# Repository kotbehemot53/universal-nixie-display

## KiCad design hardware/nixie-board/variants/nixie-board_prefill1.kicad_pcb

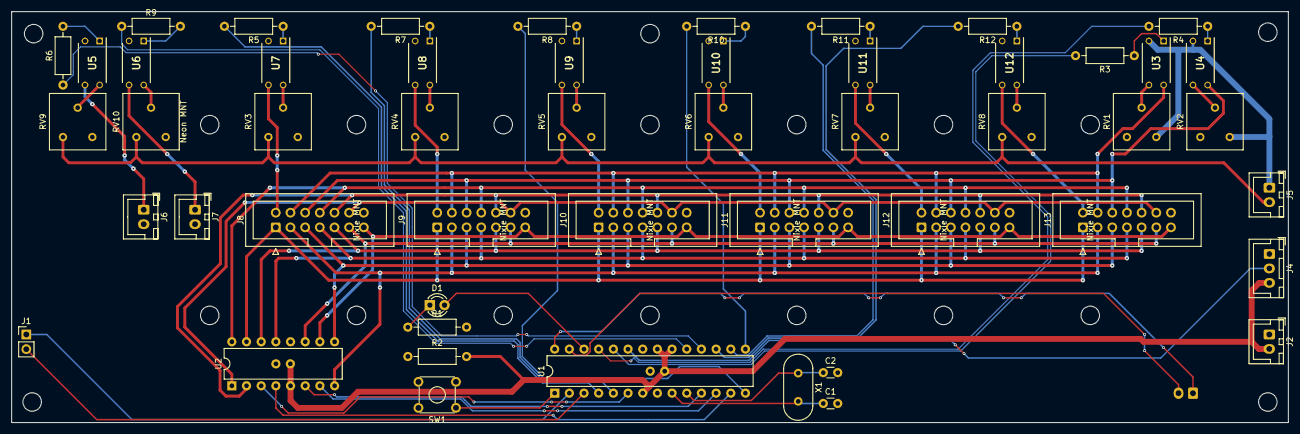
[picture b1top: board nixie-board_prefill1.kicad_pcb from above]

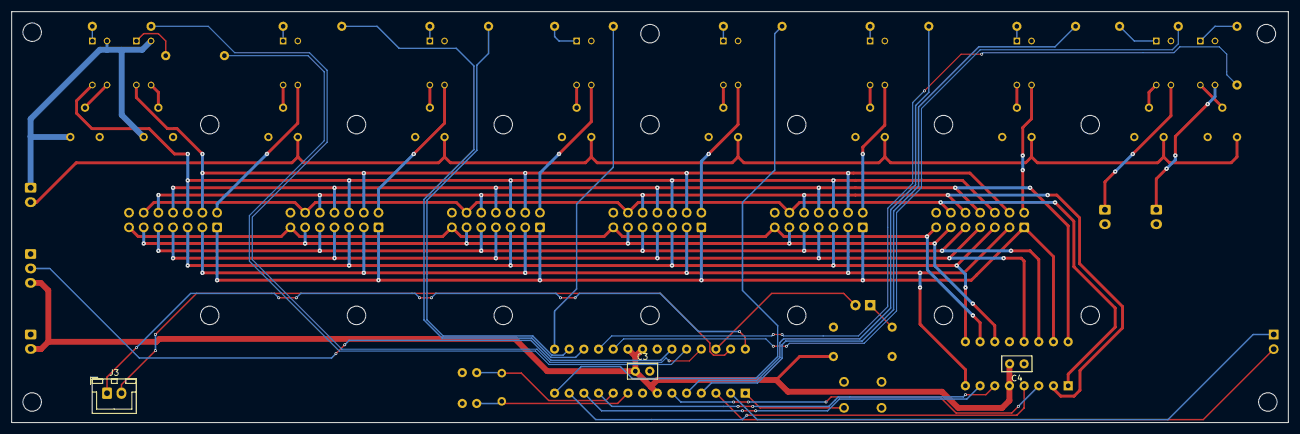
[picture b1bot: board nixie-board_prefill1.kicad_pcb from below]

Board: 2 copper layers, 221.0 x 71.1 mm, 54 parts (3 on the bottom side), 67 nets.

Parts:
C1, C2: 22pF; C_Disc_D3.0mm_W1.6mm_P2.50mm
C3, C4: 0.1uF; C_Disc_D5.0mm_W2.5mm_P2.50mm
D1: LED; LED_D3.0mm
J1: UART; PinHeader_1x02_P2.54mm_Vertical
J2: PWR; JST_XH_B2B-XH-A_1x02_P2.50mm_Vertical
J3: I2C DATA; JST_XH_B2B-XH-A_1x02_P2.50mm_Vertical
J4: BOOST C LV; JST_XH_B3B-XH-A_1x03_P2.50mm_Vertical
J5: BOOST C HV; JST_XH_B2B-XH-A_1x02_P2.50mm_Vertical
J6: NEON N0; JST_XH_B2B-XH-A_1x02_P2.50mm_Vertical
J7: NEON N1; JST_XH_B2B-XH-A_1x02_P2.50mm_Vertical
J8: L0; IDC-Header_2x07_P2.54mm_Vertical_alt_pins
J9: L1; IDC-Header_2x07_P2.54mm_Vertical_alt_pins
J10: L2; IDC-Header_2x07_P2.54mm_Vertical_alt_pins
J11: L3; IDC-Header_2x07_P2.54mm_Vertical_alt_pins
J12: L4; IDC-Header_2x07_P2.54mm_Vertical_alt_pins
J13: L5; IDC-Header_2x07_P2.54mm_Vertical_alt_pins
R1, R3, R4, R5, R6, R7, R8, R9, R10, R11, R12: 330; R_Axial_DIN0207_L6.3mm_D2.5mm_P10.16mm_Horizontal
R2: 10k; R_Axial_DIN0207_L6.3mm_D2.5mm_P10.16mm_Horizontal
RV1, RV2, RV9, RV10: 200k; Potentiometer_Bourns_3386F_Vertical
RV3, RV4, RV5, RV6, RV7, RV8: 10k; Potentiometer_Bourns_3386F_Vertical
SW1: RESET; SW_TH_Tactile_Omron_B3F-10xx
U1: ATmega328-P; DIP-28_W7.62mm
U2: K155NA1; DIP-16_W7.62mm
U3: L COMMA OPTCPLR; DIP762W56P254L469H470Q4N
U4: R COMMA OPTCPLR; DIP762W56P254L469H470Q4N
U5: N0 NEON SWITCH; DIP762W56P254L469H470Q4N
U6: N1 NEON SWITCH; DIP762W56P254L469H470Q4N
U7, U8, U9, U10, U11, U12: SFH619A; DIP762W56P254L469H470Q4N
X1: 16Mhz; Crystal_HC49-4H_Vertical

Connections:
+5V: C3.1, C4.2, J2.2, J4.3, R2.2, U1.7 (VCC), U1.20 (AVCC), U1.21 (AREF), U2.5 (VCC)
/0: J8.11 (0), J9.11 (0), J10.11 (0), J11.11 (0), J12.11 (0), J13.11 (0), U2.16 (0)
/1: J8.1, J9.1, J10.1, J11.1, J12.1, J13.1, U2.15 (1)
/2: J8.2, J9.2, J10.2, J11.2, J12.2, J13.2, U2.8 (2)
/3: J8.3, J9.3, J10.3, J11.3, J12.3, J13.3, U2.9 (3)
/4: J8.4, J9.4, J10.4, J11.4, J12.4, J13.4, U2.13 (4)
/5: J8.5, J9.5, J10.5, J11.5, J12.5, J13.5, U2.14 (5)
/6: J8.6, J9.6, J10.6, J11.6, J12.6, J13.6, U2.11 (6)
/7: J8.7, J9.7, J10.7, J11.7, J12.7, J13.7, U2.10 (7)
/8: J8.9 (8), J9.9 (8), J10.9 (8), J11.9 (8), J12.9 (8), J13.9 (8), U2.1 (8)
/9: J8.10 (9), J9.10 (9), J10.10 (9), J11.10 (9), J12.10 (9), J13.10 (9), U2.2 (9)
/A: U1.6 (PD4), U2.3 (A)
/B: U1.11 (PD5), U2.6 (B)
/C: U1.12 (PD6), U2.7 (C)
/CL: J8.13 (CL), J9.13 (CL), J10.13 (CL), J11.13 (CL), J12.13 (CL), J13.13 (CL), U3.4 (C_2)
/CR: J8.12 (CR), J9.12 (CR), J10.12 (CR), J11.12 (CR), J12.12 (CR), J13.12 (CR), U4.4 (C_2)
/D: U1.13 (PD7), U2.4 (D)
/HVENABLE: J4.2, U1.23 (PC0)
/L0: R5.2, U1.4 (PD2)
/L1: R7.2, U1.5 (PD3)
/L2: R8.2, U1.14 (PB0)
/L3: R10.2, U1.15 (PB1)
/L4: R11.2, U1.16 (PB2)
/L5: R12.2, U1.17 (PB3)
/N0: R6.1, U1.18 (PB4)
/N1: R9.1, U1.19 (PB5)
/P0: R3.2, U1.24 (PC1)
/P1: R4.2, U1.25 (PC2)
/RxD: J1.1, U1.2 (PD0)
/SCL: J3.1, U1.28 (PC5)
/SDA: J3.2, U1.27 (PC4)
/STATUS: D1.2 (A), U1.26 (PC3)
/TxD: J1.2, U1.3 (PD1)
/XTAL1: C1.1, U1.9 (XTAL1/PB6), X1.2
/XTAL2: C2.1, U1.10 (XTAL2/PB7), X1.1
/~RESET: R2.1, SW1.1, U1.1 (~RESET/PC6)
GND: C1.2, C2.2, C3.2, C4.1, J2.1, J4.1, J5.1 (HV), J6.2, J7.2, R1.2, RV1.1, RV2.1, SW1.3 (K), U1.8 (GND), U1.22 (GND), U2.12 (GND), U3.2 (C_1), U4.2 (C_1), U5.2 (C_1), U6.2 (C_1), U7.2 (C_1), U8.2 (C_1), U9.2 (C_1), U10.2 (C_1), U11.2 (C_1), U12.2 (C_1)
unnamed: D1.1 (K), R1.1
unnamed: J6.1, U5.3 (E)
unnamed: J7.1, U6.3 (E)
unnamed: J8.14 (Anode), U7.3 (E)
unnamed: J9.14 (Anode), U8.3 (E)
unnamed: J10.14 (Anode), U9.3 (E)
unnamed: J11.14 (Anode), U10.3 (E)
unnamed: J12.14 (Anode), U11.3 (E)
unnamed: J13.14 (Anode), U12.3 (E)
unnamed: R3.1, U3.1 (A)
unnamed: R4.1, U4.1 (A)
unnamed: R5.1, U7.1 (A)
unnamed: R6.2, U5.1 (A)
unnamed: R7.1, U8.1 (A)
unnamed: R8.1, U9.1 (A)
unnamed: R9.2, U6.1 (A)
unnamed: R10.1, U10.1 (A)
unnamed: R11.1, U11.1 (A)
unnamed: R12.1, U12.1 (A)
unnamed: RV1.2, U3.3 (E)
unnamed: RV2.2, U4.3 (E)
unnamed: RV3.2, U7.4 (C_2)
unnamed: RV4.2, U8.4 (C_2)
unnamed: RV5.2, U9.4 (C_2)
unnamed: RV6.2, U10.4 (C_2)
unnamed: RV7.2, U11.4 (C_2)
unnamed: RV8.2, U12.4 (C_2)
unnamed: RV9.2, U5.4 (C_2)
unnamed: RV10.2, U6.4 (C_2)
PRI_HI: J5.2, RV3.3, RV4.3, RV5.3, RV6.3, RV7.3, RV8.3, RV9.3, RV10.3

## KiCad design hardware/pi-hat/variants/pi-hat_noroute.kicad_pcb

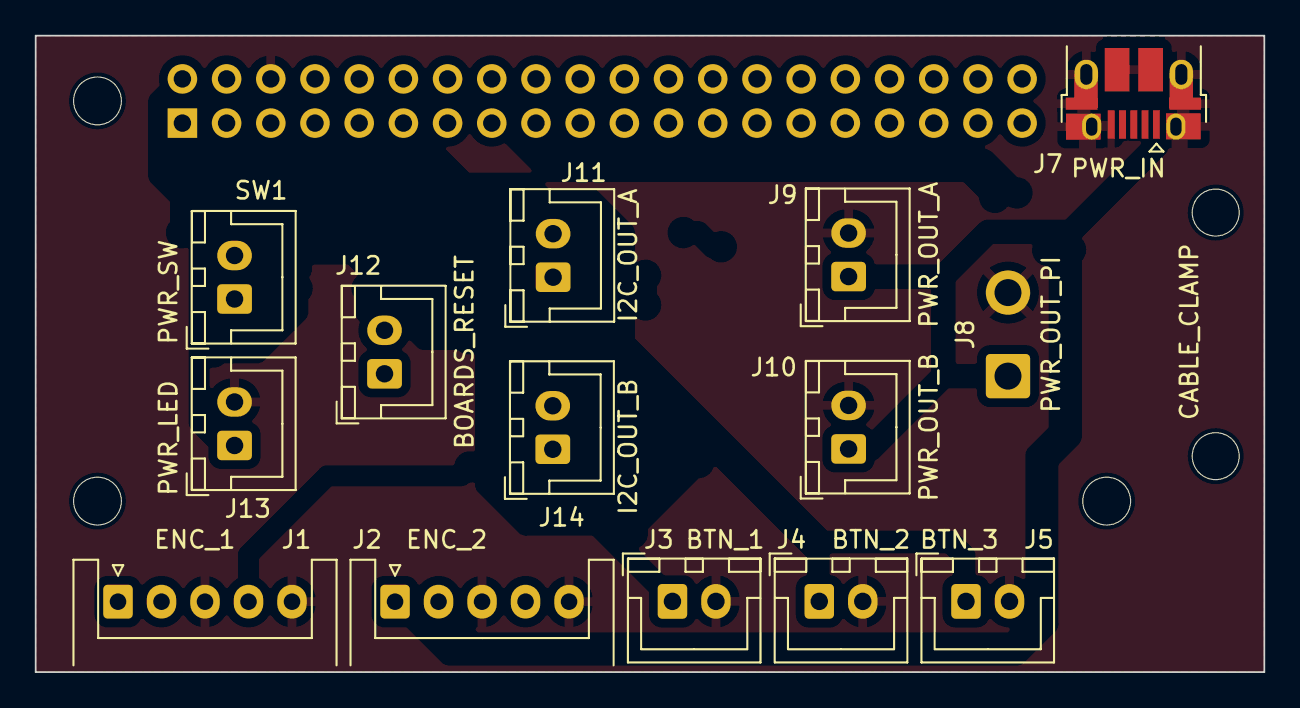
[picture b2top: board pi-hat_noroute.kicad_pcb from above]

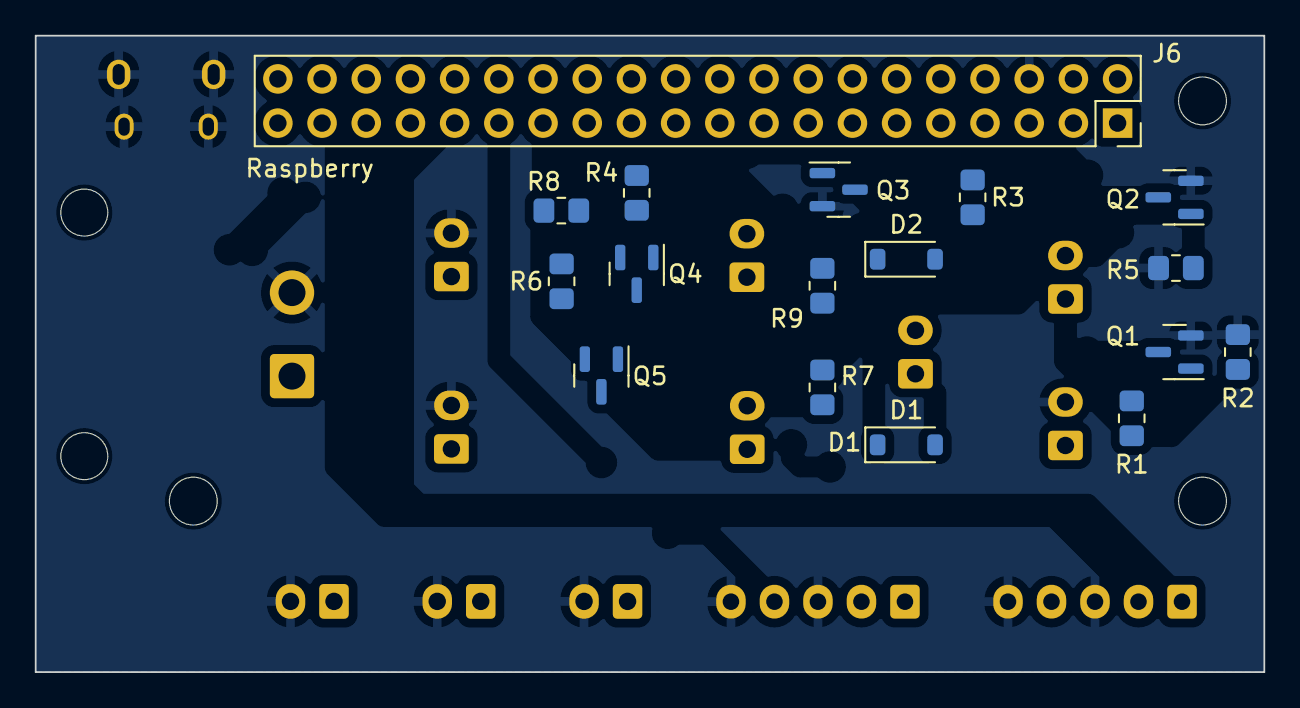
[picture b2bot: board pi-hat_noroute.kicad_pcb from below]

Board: 2 copper layers, 70.6 x 36.6 mm, 33 parts (17 on the bottom side), 27 nets, no tracks yet.

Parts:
A2: Raspberry_Pi_Zero_Socketed_THT_FaceDown_MountingH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; Raspberry_Pi_Zero_Socketed_THT_FaceDown_MountingHoles
CH1: CABLE_CLAMP; CableClamp_P14mm
D1, D2: 1N4148W; D_SOD-123
J1: ENC_1; JST_XH_S5B-XH-A_1x05_P2.50mm_Horizontal
J2: ENC_2; JST_XH_S5B-XH-A_1x05_P2.50mm_Horizontal
J3: BTN_1; JST_XH_B2B-XH-A_1x02_P2.50mm_Vertical
J4: BTN_2; JST_XH_B2B-XH-A_1x02_P2.50mm_Vertical
J5: BTN_3; JST_XH_B2B-XH-A_1x02_P2.50mm_Vertical
J6: Raspberry; PinSocket_2x20_P2.54mm_Vertical
J7: PWR_IN; USB_Micro-B_Amphenol_10103594-0001LF_Horizontal
J8: PWR_OUT_PI; SolderWire-0.75sqmm_1x02_P4.8mm_D1.25mm_OD2.3mm
J9: PWR_OUT_A; JST_XH_B2B-XH-A_1x02_P2.50mm_Vertical
J10: PWR_OUT_B; JST_XH_B2B-XH-A_1x02_P2.50mm_Vertical
J11: I2C_OUT_A; JST_XH_B2B-XH-A_1x02_P2.50mm_Vertical
J12: BOARDS_RESET; JST_XH_B2B-XH-A_1x02_P2.50mm_Vertical
J13: PWR_LED; JST_XH_B2B-XH-A_1x02_P2.50mm_Vertical
J14: I2C_OUT_B; JST_XH_B2B-XH-A_1x02_P2.50mm_Vertical
Q1, Q2, Q3: BC846; SOT-23
Q4, Q5: BSS138; SOT-23
R1, R3, R6, R7, R8, R9: 10k; R_0805_2012Metric_Pad1.20x1.40mm_HandSolder
R2, R4, R5: 100k; R_0805_2012Metric_Pad1.20x1.40mm_HandSolder
SW1: PWR_SW; JST_XH_B2B-XH-A_1x02_P2.50mm_Vertical

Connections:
+3.3V: J6.1, Q4.1 (G), Q5.1 (G), R6.2, R8.2
+5V: J6.2, R7.1, R9.1, SW1.2
/BTN_1: J3.1, J6.3
/BTN_2: J4.1, J6.7
/BTN_3: J5.1, J6.11
/ENC_1_A: J1.1, J6.31
/ENC_1_B: J1.2, J6.37
/ENC_1_BTN: J1.4, J6.22
/ENC_2_A: J2.1, J6.13
/ENC_2_B: J2.2, J6.15
/ENC_2_BTN: J2.4, J6.29
/EXT_5V: J7.1 (VBUS), J8.1, J9.1, J10.1
/I2C_CLK: J6.28, Q4.2 (S), R6.1
/I2C_CLK_5V: J11.2, J14.2, Q4.3 (D), R7.2
/I2C_DATA: J6.27, Q5.2 (S), R8.1
/I2C_DATA_5V: J11.1, J14.1, Q5.3 (D), R9.2
/PI_ALIVE: J6.32, R4.2
/PI_ON_OFF: J6.5, Q1.3 (C)
/PWR_LED: J6.8, J13.1
/SW_ON_OFF: R1.1, R2.1, R3.2, SW1.1
/~RESET A: D1.2 (A), J12.1
/~RESET B: D2.2 (A), J12.2
GND: J1.3, J1.5, J2.3, J2.5, J3.2, J4.2, J5.2, J6.6, J7.5 (GND), J7.6 (Shield), J8.2, J9.2, J10.2, J13.2, Q1.2 (E), Q2.2 (E), Q3.2 (E), R2.2, R5.2
unnamed: D1.1 (K), D2.1 (K), Q3.3 (C)
unnamed: Q1.1 (B), R1.2
unnamed: Q2.1 (B), R4.1, R5.1
unnamed: Q2.3 (C), Q3.1 (B), R3.1

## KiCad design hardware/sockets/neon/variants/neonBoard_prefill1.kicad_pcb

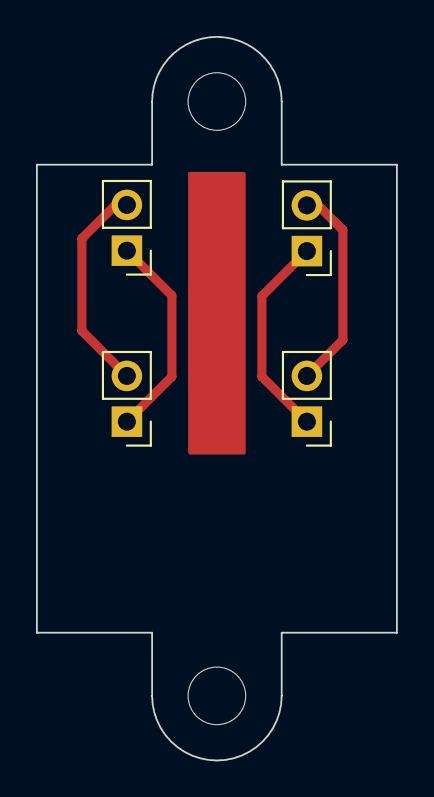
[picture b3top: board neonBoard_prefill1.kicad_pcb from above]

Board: 2 copper layers, 20.0 x 40.2 mm, 4 parts (0 on the bottom side), 4 nets.

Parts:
J0: CN0; PinHeader_1x02_P2.54mm_Vertical
J1: CN1; PinHeader_1x02_P2.54mm_Vertical
NE0: N0; PinHeader_1x02_P2.54mm_Vertical
NE1: N1; PinHeader_1x02_P2.54mm_Vertical

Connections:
/N0A: J0.2, NE0.2
/N0K: J0.1, NE0.1
/N1A: J1.2, NE1.2
/N1K: J1.1, NE1.1
